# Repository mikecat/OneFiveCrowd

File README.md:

OneFiveCrowd
============

[https://onefivecrowd.mikecat.work/](https://onefivecrowd.mikecat.work/)

## これは何？

[IchigoJam](https://ichigojam.net/)シミュレータ。

IchigoJam向けのプログラムをブラウザ上で実行する。

※「IchigoJam」はjig.jpの登録商標です。

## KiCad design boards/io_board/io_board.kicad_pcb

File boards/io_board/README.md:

I/O Board for OneFiveCrowd
==========================

MCP2221とI/Oエキスパンダを用い、USB経由でのI/Oを実現します。

ハードウェアの制約により、以下の制約があります。

* 5Vトレラントではありません。
* PWMは非対応です。
* BTN・IN2・IN3以外のADCは非対応です。
* IN2・IN3のプルアップは非対応です。
* DACでは1種類の値しか出力できません。

[IchigoJam T ガーバーデータ](https://ichigojam.net/download.html) ([CC BY](https://creativecommons.org/licenses/by/4.0/deed.ja) [aitendo](http://www.aitendo.com/) & [jig.jp](http://jig.jp/)) を参照し、互換性のある端子および穴の配置としています。

さらに、I2C用のGROVEコネクタおよび Digilent Pmod™ Interface Specification を参考にしたコネクタも用意しています。

## リソース

* [回路図](io_board_v1_0.pdf)
* [ガーバーファイル](io_board-gerver_v1_0.zip)

## パーツリスト

|リファレンス|種類|値|
|---|---|---|
|U1|IC|USBブリッジ MCP2221A-I/SL (SOIC 1.27mmピッチ)|
|U2|IC|I/Oエキスパンダ MCP23008-E/SO (SOIC 1.27mmピッチ)|
|U3|IC|3端子レギュレータ 3.3V NJM2845DL1-33|
|R1、R2|抵抗|5.1kΩ 1/4Wサイズ (長さ6.3mm)|
|R3|抵抗|1MΩ 1/4Wサイズ (長さ6.3mm)|
|R4|抵抗|LED用 (抵抗値はお好みで) 1/4Wサイズ (長さ6.3mm)|
|R5、R6|抵抗|10kΩ 1/4Wサイズ (長さ6.3mm)|
|C1|コンデンサ|0.33μF 5mmピッチ|
|C2|コンデンサ|2.2μF 5mmピッチ|
|C3、C4|コンデンサ|0.1μF 2.54mmピッチ|
|D1|LED|お好みで (砲弾型Φ5mm推奨)|
|SW1|スイッチ|タクトスイッチ 6mm DTS-6 (TS-0606) シリーズ|
|SW2|スイッチ|スライドスイッチ 2.54mmピッチ 1回路2接点 (SS-12D00G3 など)|
|J1|USBコネクタ|秋月 K-15426 / K-13080|
|J2、J3|ピンソケット|2.54mmピッチ 1×14|
|J4|ピンソケット|2.54mmピッチ 1×5|
|J5|ピンソケット|2.54mmピッチ L型 1×6|
|J6|コネクタ|GROVE 4ピンコネクタ 垂直タイプ|

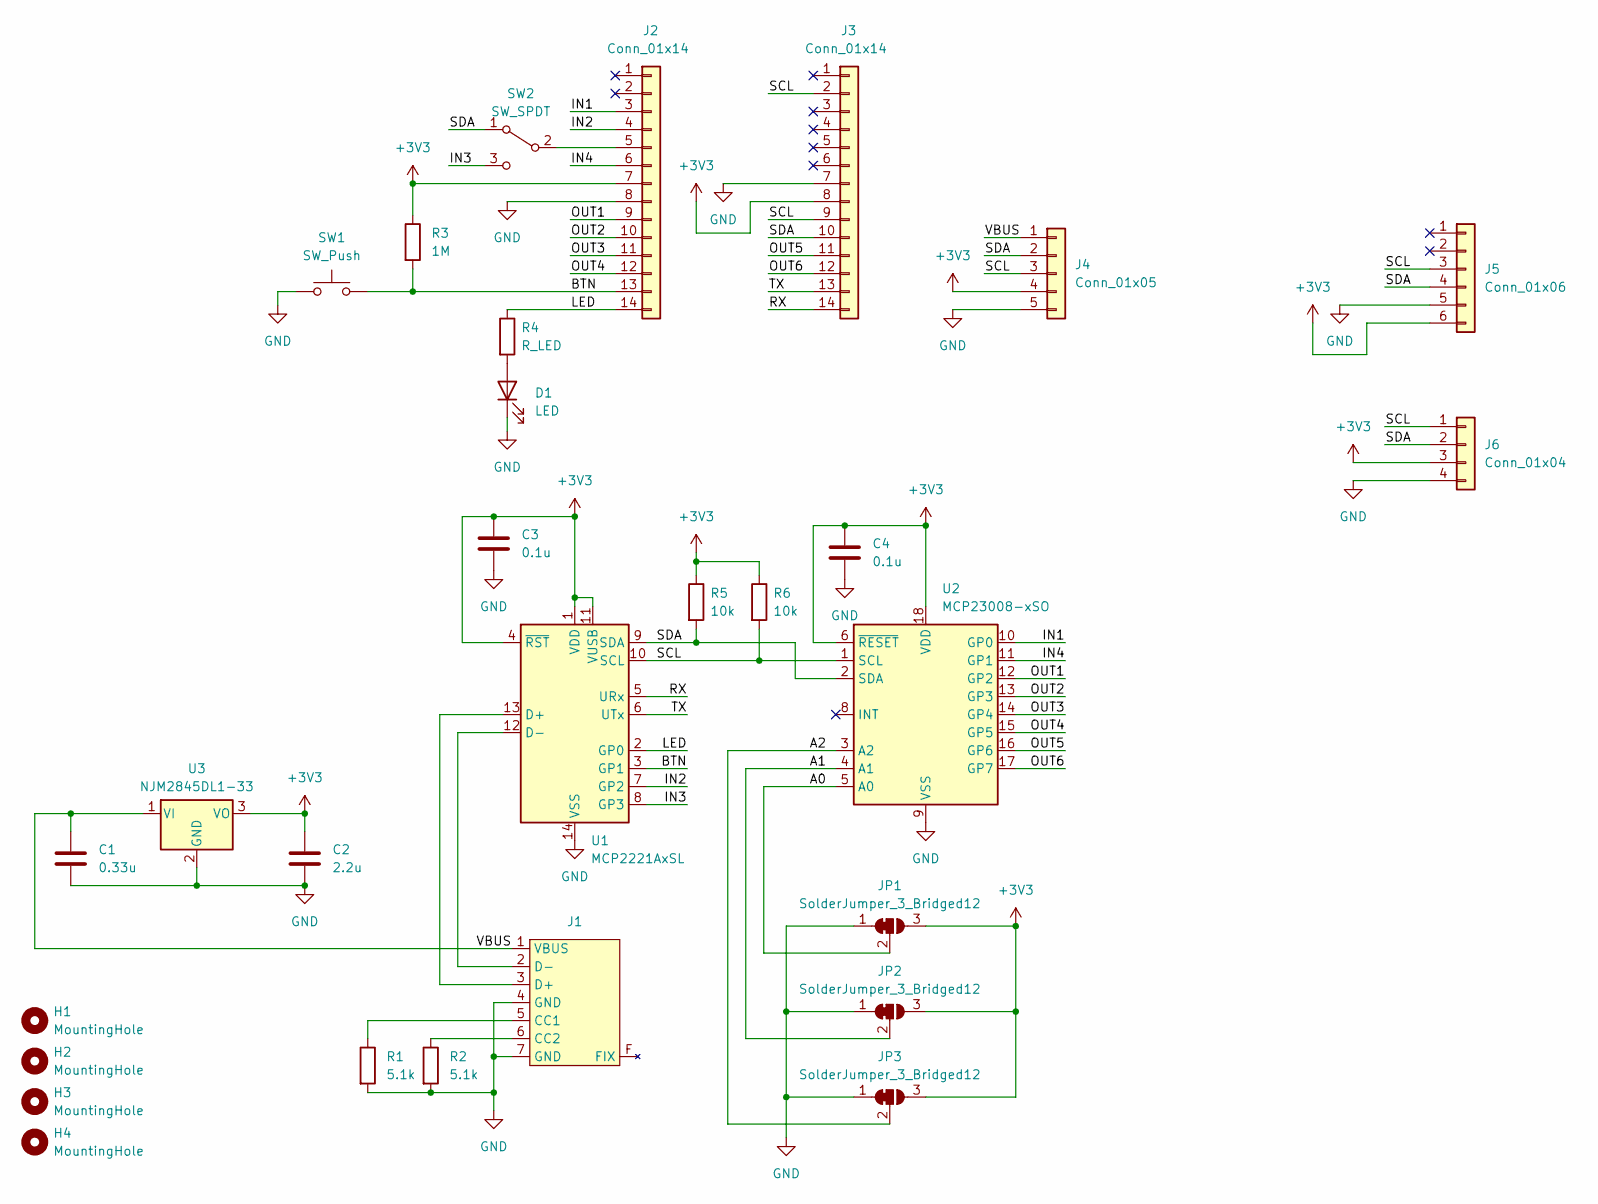
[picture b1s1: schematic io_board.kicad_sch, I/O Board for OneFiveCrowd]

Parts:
C1: 0.33u; C_Disc_D5.1mm_W3.2mm_P5.00mm
C2: 2.2u; C_Disc_D5.1mm_W3.2mm_P5.00mm
C3, C4: 0.1u; C_Disc_D3.8mm_W2.6mm_P2.50mm
D1: LED; LED_D5.0mm
H1, H2, H3, H4: MountingHole; MountingHole_3.2mm_M3
J1: AE-USB2.0-TYPE-C
J2, J3: Conn_01x14; PinSocket_1x14_P2.54mm_Vertical
J4: Conn_01x05; PinSocket_1x05_P2.54mm_Vertical
J5: Conn_01x06; PinSocket_1x06_P2.54mm_Vertical
J6: Conn_01x04; JST_PH_B4B-PH-K_1x04_P2.00mm_Vertical
JP1, JP2, JP3: SolderJumper_3_Bridged12; SolderJumper-3_P1.3mm_Bridged12_RoundedPad1.0x1.5mm_NumberL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
R1, R2: 5.1k; R_Axial_DIN0207_L6.3mm_D2.5mm_P10.16mm_Horizontal
R3: 1M; R_Axial_DIN0207_L6.3mm_D2.5mm_P10.16mm_Horizontal
R4: R_LED; R_Axial_DIN0207_L6.3mm_D2.5mm_P10.16mm_Horizontal
R5, R6: 10k; R_Axial_DIN0207_L6.3mm_D2.5mm_P10.16mm_Horizontal
SW1: SW_Push; SW_PUSH_6mm_H5mm
SW2: SW_SPDT; PinHeader_1x03_P2.54mm_Vertical
U1: MCP2221AxSL; SOIC-14_3.9x8.7mm_P1.27mm
U2: MCP23008-xSO; SOIC-18W_7.5x11.6mm_P1.27mm
U3: NJM2845DL1-33; TO-252-2

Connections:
+3V3: C2.1, C3.1, C4.1, J2.7, J3.8, J4.4, J5.6, J6.3, JP1.3 (B), JP2.3 (B), JP3.3 (B), R3.1, R5.1, R6.1, U1.1 (VDD), U1.4 (~RST), U1.11 (VUSB), U2.6 (~RESET), U2.18 (VDD), U3.3 (VO)
/A0: JP1.2 (C), U2.5 (A0)
/A1: JP2.2 (C), U2.4 (A1)
/A2: JP3.2 (C), U2.3 (A2)
/BTN: J2.13, R3.2, SW1.2, U1.3 (GP1)
/IN1: J2.3, U2.10 (GP0)
/IN2: J2.4, U1.7 (GP2)
/IN3: SW2.3 (C), U1.8 (GP3)
/IN4: J2.6, U2.11 (GP1)
/LED: J2.14, R4.1, U1.2 (GP0)
/OUT1: J2.9, U2.12 (GP2)
/OUT2: J2.10, U2.13 (GP3)
/OUT3: J2.11, U2.14 (GP4)
/OUT4: J2.12, U2.15 (GP5)
/OUT5: J3.11, U2.16 (GP6)
/OUT6: J3.12, U2.17 (GP7)
/RX: J3.14, U1.5 (URx)
/SCL: J3.2, J3.9, J4.3, J5.3, J6.1, R6.2, U1.10 (SCL), U2.1 (SCL)
/SDA: J3.10, J4.2, J5.4, J6.2, R5.2, SW2.1 (A), U1.9 (SDA), U2.2 (SDA)
/TX: J3.13, U1.6 (UTx)
/VBUS: C1.1, J1.1 (VBUS), J4.1, U3.1 (VI)
GND: C1.2, C2.2, C3.2, C4.2, D1.1 (K), J1.4 (GND), J1.7 (GND), J2.8, J3.7, J4.5, J5.5, J6.4, JP1.1 (A), JP2.1 (A), JP3.1 (A), R1.2, R2.2, SW1.1, U1.14 (VSS), U2.9 (VSS), U3.2 (GND)
unnamed: D1.2 (A), R4.2
unnamed: J1.5 (CC1), R1.1
unnamed: J1.6 (CC2), R2.1
unnamed: J1.3 (D+), U1.13 (D+)
unnamed: J1.2 (D-), U1.12 (D-)
unnamed: J2.5, SW2.2 (B)

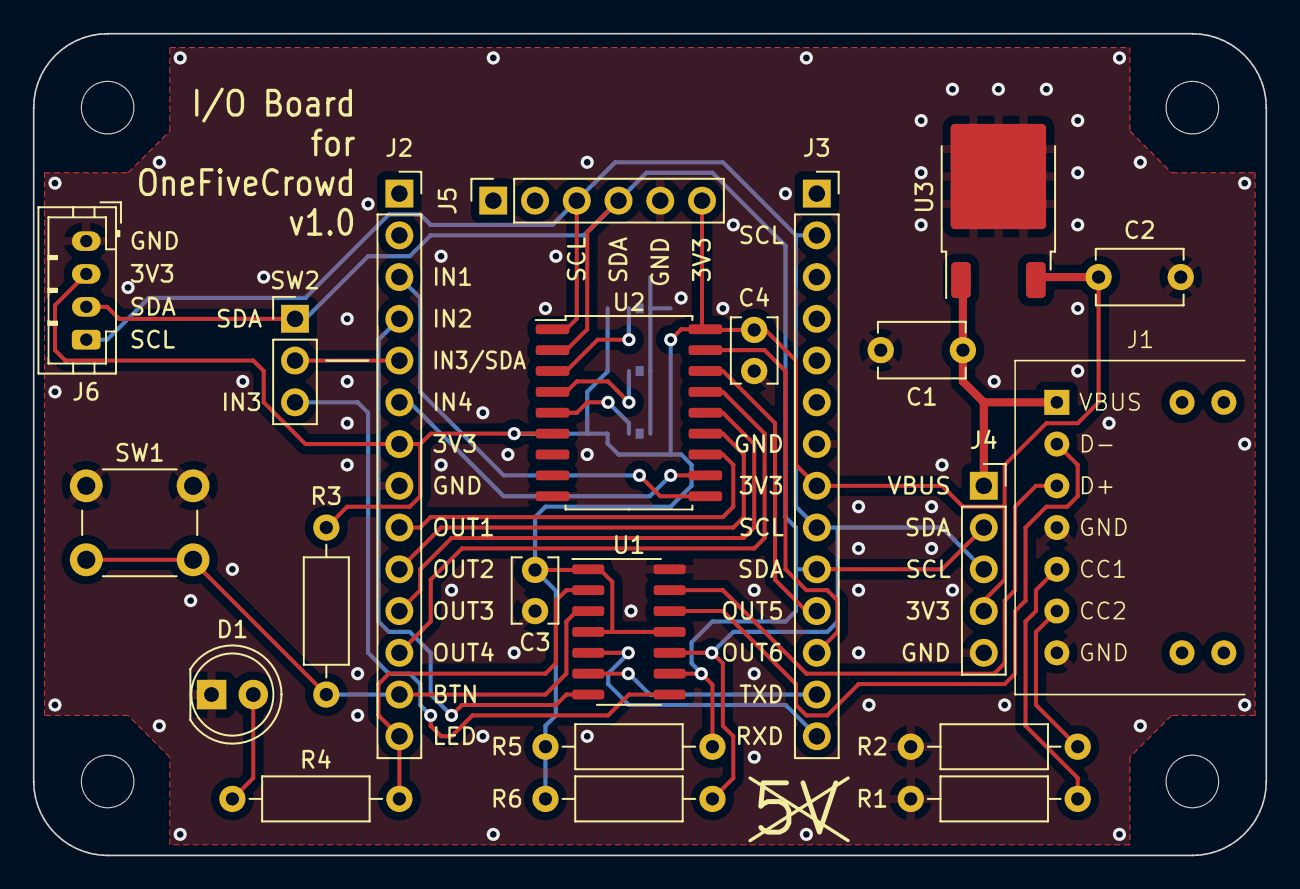
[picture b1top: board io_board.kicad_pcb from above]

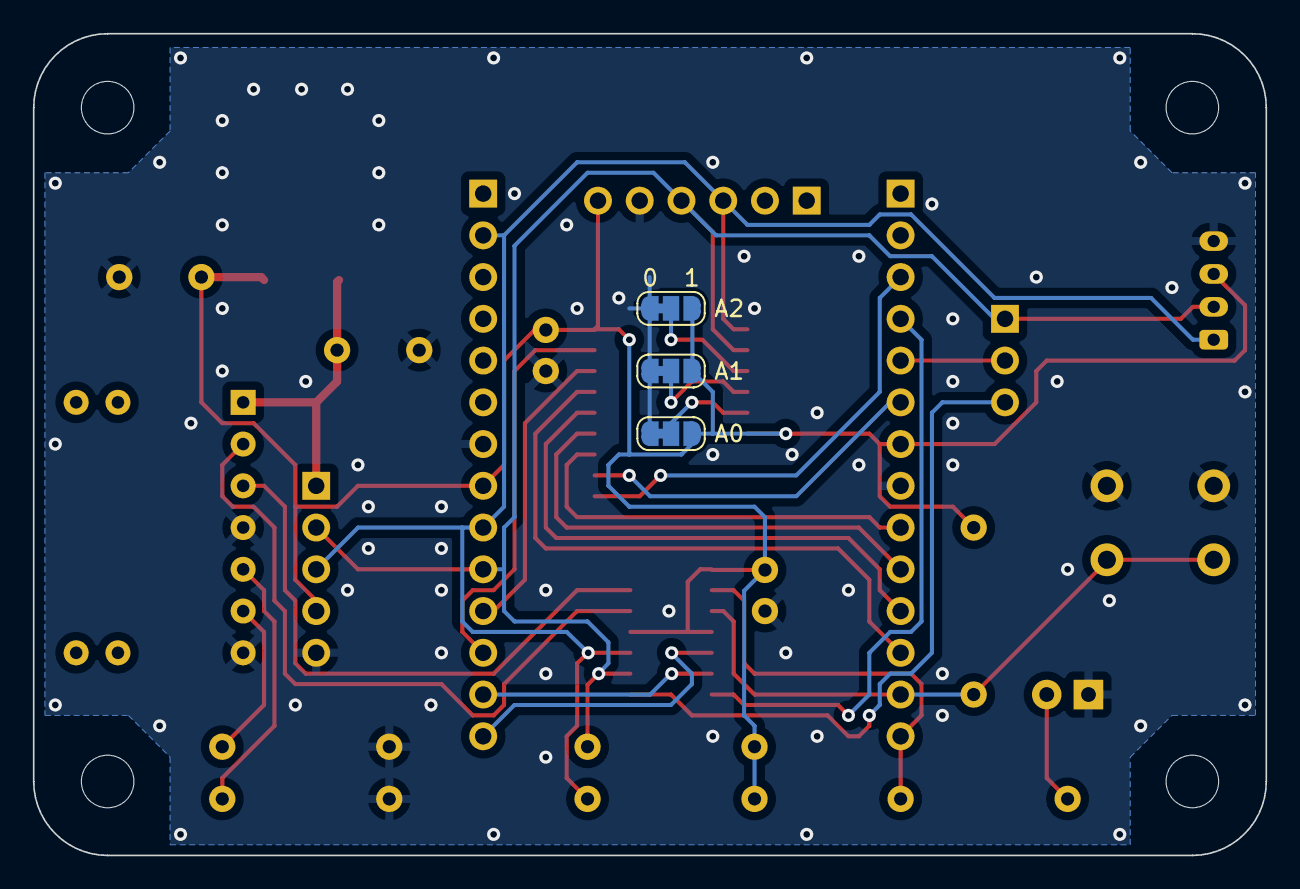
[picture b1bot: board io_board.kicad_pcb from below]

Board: 2 copper layers, 75.0 x 50.0 mm, 29 parts (3 on the bottom side), 28 nets.

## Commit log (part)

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2019-06-13 add link
2019-06-14 introduce key buffer
2019-06-14 swap alphabet case on input
2019-06-14 support key modifier
2019-06-14 implement speclal characters input
2019-06-14 extract enqueueKey()
2019-06-14 implement cursor move by one
2019-06-14 implement Backspace
2019-06-14 implement Delete
2019-06-14 implement codes to ignore
2019-06-14 fix code to send on F1
2019-06-14 implement newline
2019-06-15 implement absolute move of cursor
2019-06-15 implement insert space
2019-06-15 improve character insert behavior
2019-06-15 implement line split
2019-06-16 read command from screen on Enter pressed
2019-06-16 add lexer
2019-06-17 write BNF and add missed tokens
2019-06-27 bugfix: don't delete cursor not shown
2019-06-27 use object instead of array to represent tokens
2019-06-27 add token kind
2019-07-25 allow invalid token to be lexed
2019-07-25 have it emit parse result
2019-07-25 improve BNF
2019-07-25 enable to parse comment
2019-07-25 rename a token
2019-07-25 enable to parse empty command
2019-07-25 enable to parse label_definition
2019-07-25 extract checkTokenKind
2019-07-25 enable to parse IF command (with minimum expr parsing)
2019-07-25 enable to parse array as variable
2019-07-26 enable to parse FOR command
2019-07-26 enable to parse PRINT command
2019-07-26 enable to parse general commands
2019-07-26 improve BNF and prepare function_name
2019-07-27 move variableIndice
2019-09-22 use let/const instead of var
2019-09-22 improve formatting
2019-09-22 extract putString()
2019-09-23 add token & node object definition
2019-09-23 enable to edit program
2021-06-30 improve parser and enable to run some commands
2021-07-01 implement operators
2021-07-01 implement variable in expression and LET command
2021-07-01 bugfix in hexadecimal number
2022-12-26 improve compileLine()
    have the function return a program to throw Syntax error
    instead of directly throwing Syntax error.
    This will allow it to execute stored program until hitting the line
    that actually contains Syntax error.
2022-12-26 make compilation result logging opt-in
2022-12-26 support RUN command
    * compilation of stored program
    * print exception with the line that threw the exception
    * have compileProgram() return the result with compiled source
    * check prgDirty
2022-12-26 fix string address
2022-12-26 fix address for RAM contents
2022-12-26 create functions for commands and functions
2022-12-26 add command CLEAR
2022-12-26 add commands GOTO and END
2022-12-26 remove extra commandRUN() function
2022-12-27 add LOCATE and LC commands
2022-12-27 add function RND
2022-12-27 make compiled functions async
2022-12-28 add command CLT and function TICK
2022-12-28 add command WAIT
2022-12-28 show cursor only if waiting for key input
2022-12-28 add function BTN
2022-12-28 add command LIST
2022-12-28 reject invalid line number for editing
2022-12-28 bugfix: lines whose length is multiple of screen width were not recognized
2022-12-28 add function FREE
2022-12-28 add functions
    INKEY / ASC / ABS / LINE / LEN / COS / SIN
2022-12-28 move commandPOKE to match the order in Compiler.js
2022-12-28 add constant VIRTUAL_RAM_OFFSET
2022-12-28 add command HELP
2022-12-28 add tokens for commands KBD and DAC (no implementation yet)
2022-12-28 remove "Not implemented: LET"
2022-12-29 add commands FOR and NEXT
2022-12-29 add command GOSUB/GSB and RETURN/RTN
2022-12-29 add command COPY
2022-12-29 add command SCROLL
2022-12-29 add function POINT
2022-12-29 add command SRND
    based on this article:
    https://qiita.com/mikecat_mixc/items/3be6ad040e93be5dfa15
2022-12-29 add PRINT modifiers
2022-12-29 add command OK
2022-12-29 add command RESET
2022-12-30 improve response
    * break from loop based on time instead of number of iterations
    * use the technique from
    https://qiita.com/hiruberuto/items/0b89c36556cadbd751e2
2022-12-30 add wait when INKEY()=0
2022-12-30 add IchigoJam BASIC 1.4 font
2022-12-30 add function VER
2022-12-30 add command STOP
    IchigoJam BASIC prints "Syntax error" for the STOP command,
    but this looks confusing.
    Therefore, OneFiveCrowd won't do this and will use clearer message.
2022-12-30 add command CONT
2023-04-01 fix error at comment-only line
    example (previously error occured at line 20):
    10 ?1
    20 'A
2023-04-01 fix style attribute
2023-04-01 add "input text" feature
2023-04-01 add Ed25519 functions
    based on https://fukuno.jig.jp/3902
    implemented:
    * SEC.PUBKEY (command)
    * SEC.SIGN (command)
    * SEC.VERIFY (function)
2023-04-01 avoid error on executing space-only line
2023-04-29 fix 0x10 behavior on empty last line ( #1 )
2023-04-29 fix position of </head> ( #4 )
2023-06-20 add command INPUT
2023-06-20 fix PRINT command
    ?"HOGE"
    wrongly printed HOG
    this fix will make it correctly print HOGE
2023-06-21 add function LANG()
2023-06-21 support high characters in "input text"
2023-06-21 fix lexer
    add "!" to token list
    for example, fix execution of ?!0
2023-06-21 add VIDEO command
2023-06-22 add BEEP command and SOUND function
2023-06-22 fix ELSE after GOSUB
    example:
    10 IF 1 GOSUB 30 ELSE GOSUB 40
    20 END
    30 ?"YES":RETURN
    40 ?"FAIL":RETURN
    this program printed "FAIL" while it shouldn't
2023-06-23 move things to docs/
2023-06-23 create CSS file ( #2 )
2023-06-23 set viewport, add UI elements (don't work)
2023-06-23 add LED command
2023-06-23 implement volume controller
2023-07-04 implement control tab switching
2023-07-04 enable to select font to use
2023-07-04 enable to select MML interpretation
2023-07-05 save configuration to localStorage
2023-07-05 improve behavior of NEW
    NEW:?1
    now doesn't print "1" (match with 1.4.1 and 1.4.3web)
2023-07-06 fix comment
2023-07-07 add file functions
    * SAVE
    * LOAD
    * FILES
    * LRUN
    * FILE()
2023-07-07 improve behavior of IF
    IF 0 ?1:IF 1 ?2 ELSE ?3
    should print nothing, printed 3
2023-07-07 improve behavior of LOAD
    stop execution after LOAD
2023-07-07 improve behavior of LOCATE/LC
    * support one-argument format
    * support cursor switch
2023-07-08 improve screen keyboard behavior
2023-07-08 have links be opened in new tabs
    prevent accidental loss of progress by moving to another page
2023-07-08 improve behavior of LRUN
2023-07-08 prevent text selection on tab buttons
2023-07-09 enable to select screen keyboard layout from HTML element
2023-07-10 add function USR (no API support yet)
2023-07-10 add modulo to SIN and COS
2023-07-10 print address on invalid memory access
2023-07-11 implement RV32C for USR()
2023-07-11 minor fixes
2023-07-11 add IchigoCake memory mode
2023-07-11 fix event handler
2023-07-11 add comments
2023-07-11 change behavior of inkey API to match 1.4.1
    before change (same as BASIC INKEY() function):
    no input: return 0
    0 is entered: return #100
    after change (match 1.4.1):
    no input: return -1
    0 is entered: return 0
2023-07-12 add indentation to HTML
2023-07-12 improve UART send behavior
2023-07-12 avoid reading back in canvas invert operation
2023-07-15 add io_board
2023-07-16 have RAM write from USR() set dirty flags
2023-07-16 fix RV32C memory write
2023-07-17 improve text import/export table
    defined import/export characters for 0x00-0x1f and 0x7f
2023-07-17 add program/screen export function
2023-07-17 improve screen export
    prevent from emitting empty line for empty screen
2023-07-19 add virtual EEPROM
2023-07-19 change virtual EEPROM behaviors
    * treat unspecified data from virtual EEPROM as 0 instead of 0xff
    * trim trailing zero on saving and exporting
    * automatically connect virtual EEPROM on creating new one
2023-07-21 improve behavior of LIST
    wait after each (screen height - 2) lines, not fixed number of lines
2023-07-21 improve behavior of FILE
    * wait after (screen height - 2) line, not fixed amount
    * cut output of each lines at (screen width - 2) characters
2023-07-21 treat only whitespaces as blank characters
    Don't consider tabs and newlines as blanks
    Test:
    10 A="":GOTO 1
    RUN
    This prints "Line error", but set the address to the variable A.
    Then,
2023-07-21 add command RENUM
2023-07-23 add command UART
2023-07-23 add await to a putString call
2023-07-23 input tab, not spaces, when Tab key is pressed
2023-07-23 enable to switch insert/overwrite mode
2023-07-23 bugfix special character input from screen keyboard
2023-07-23 implement roman input
2023-07-25 fix roman input behavior
    was removed more characters than it should remove when entering
    small tsu by entering same characters twice
2023-07-27 Create CNAME
2023-07-27 migrate to custom domain
2023-07-28 avoid responding to comment-only line
2023-07-28 add virtual MixJuice
2023-07-29 improve HELP command in Cake mode
2023-07-30 bugfix putChar()
2023-07-30 update VirtualPanCake
    * implement LINE and CIRCLE commands
    * bugfix argument parsing for text commands
2023-07-30 VirtualPanCake: reduce meaningless screen update
2023-07-30 update VirtualPanCake
    * add sprite transparent color information to resource file
    * change resource variable name
    * implement STAMPS command
2023-07-31 prevent Syntax error from blocking execution of valid part
2023-07-31 VirtualPanCake: add STAMP and STAMP1 commands
2023-07-31 VirtualPanCake: add SPRITE START command
2023-07-31 VirtualPanCake: have PC RESET reset sprite enable status
2023-07-31 fix typo
2023-07-31 VirtualPanCake: add SPRITE * commands
2023-08-01 add PC.* commands
2023-08-01 minor improvement of keyDown()
2023-08-01 split system configuration to behavior and environment
2023-08-01 add input from the clipboard feature
2023-08-01 keyRomanInput(): use === instead of ==
2023-08-01 improve "share by URL" UI
2023-08-02 add command SWITCH
2023-08-11 VirtualPanCake: add sound commands
    * SOUND
    * SOUND1
    * MUSIC SCORE
    * MUSIC PLAY
    * MUSIC LOAD
2023-08-11 improve lexing of token after hexadecimal number
    Fix Syntax error of
    IF 1 ?#12 ELSE ?#34
    and
    IF#1AND#2?1
    This makes it also accept
    IF #1 DRAW 60,10
2023-08-11 bugfix: PC.MSCORE didn't emit LF
2023-08-11 improve text import compatibility with IchigoJam web
    This includes breaking changes for import/export of some of 0x00-0x1f
2023-08-12 add ioManager
    also added CLO command
2023-08-12 change port status notification format
2023-08-12 have LED use ioManager
2023-08-14 add empty option to createPortSelect()
2023-08-14 bugfix and improve addPorts()
2023-08-15 improve ioManager
    * introduce "port group"
    * bugfix createPortSelect() with selectedPort = ""
2023-08-15 improve I/O port DOM initialization
    Have it show current status of ports on initialization
2023-08-15 bugfix lexer
    enable to parse tokens with spaces like "GOT O"
2023-08-16 implement I/O commands and functions
    * OUT
    * PWM
    * DAC
    * IN()
    * ANA()
2023-08-16 have BTN() reflect port status
2023-09-03 fix virtual memory size for Cake
2023-09-03 add functions I2CR and I2CW
2023-09-05 add IoT.IN() and IoT.OUT
2023-09-05 implement APIs for USR()
    * out
    * in
    * pwm
    * ana
2023-09-05 add WS.LED command and ws_led API
2023-09-05 use === instead of ==
2023-09-05 remove console.log for debugging
2023-09-05 reorder I/O UI
2023-09-13 add English translation
2023-09-15 add padding to canvases theirselves instead of CSS
2023-09-15 fix main screen drawing
2023-11-13 add virtual I/O device "Click Button"
2023-11-13 fix: connection status of Click Button was ignored
2023-11-13 improve Click Button behavior
2023-11-23 add Virtual FUll Color LED
2023-11-23 enable to export Virtual Full-Color LED configuration in Share via URL
2023-11-23 disable Virtual Full-Color LED configuration exporting by default
2024-01-01 improve text input function: remove focus from the button after input)
2024-01-01 enable to use "," instead of "=" in FOR command
2024-05-04 fix negative arugment for USR was not correctly passed
    this program should print -1, but was printing 0
    10 POKE#700,#00,#0C,#70,#47
    20 PRINT USR(#700,-1)
